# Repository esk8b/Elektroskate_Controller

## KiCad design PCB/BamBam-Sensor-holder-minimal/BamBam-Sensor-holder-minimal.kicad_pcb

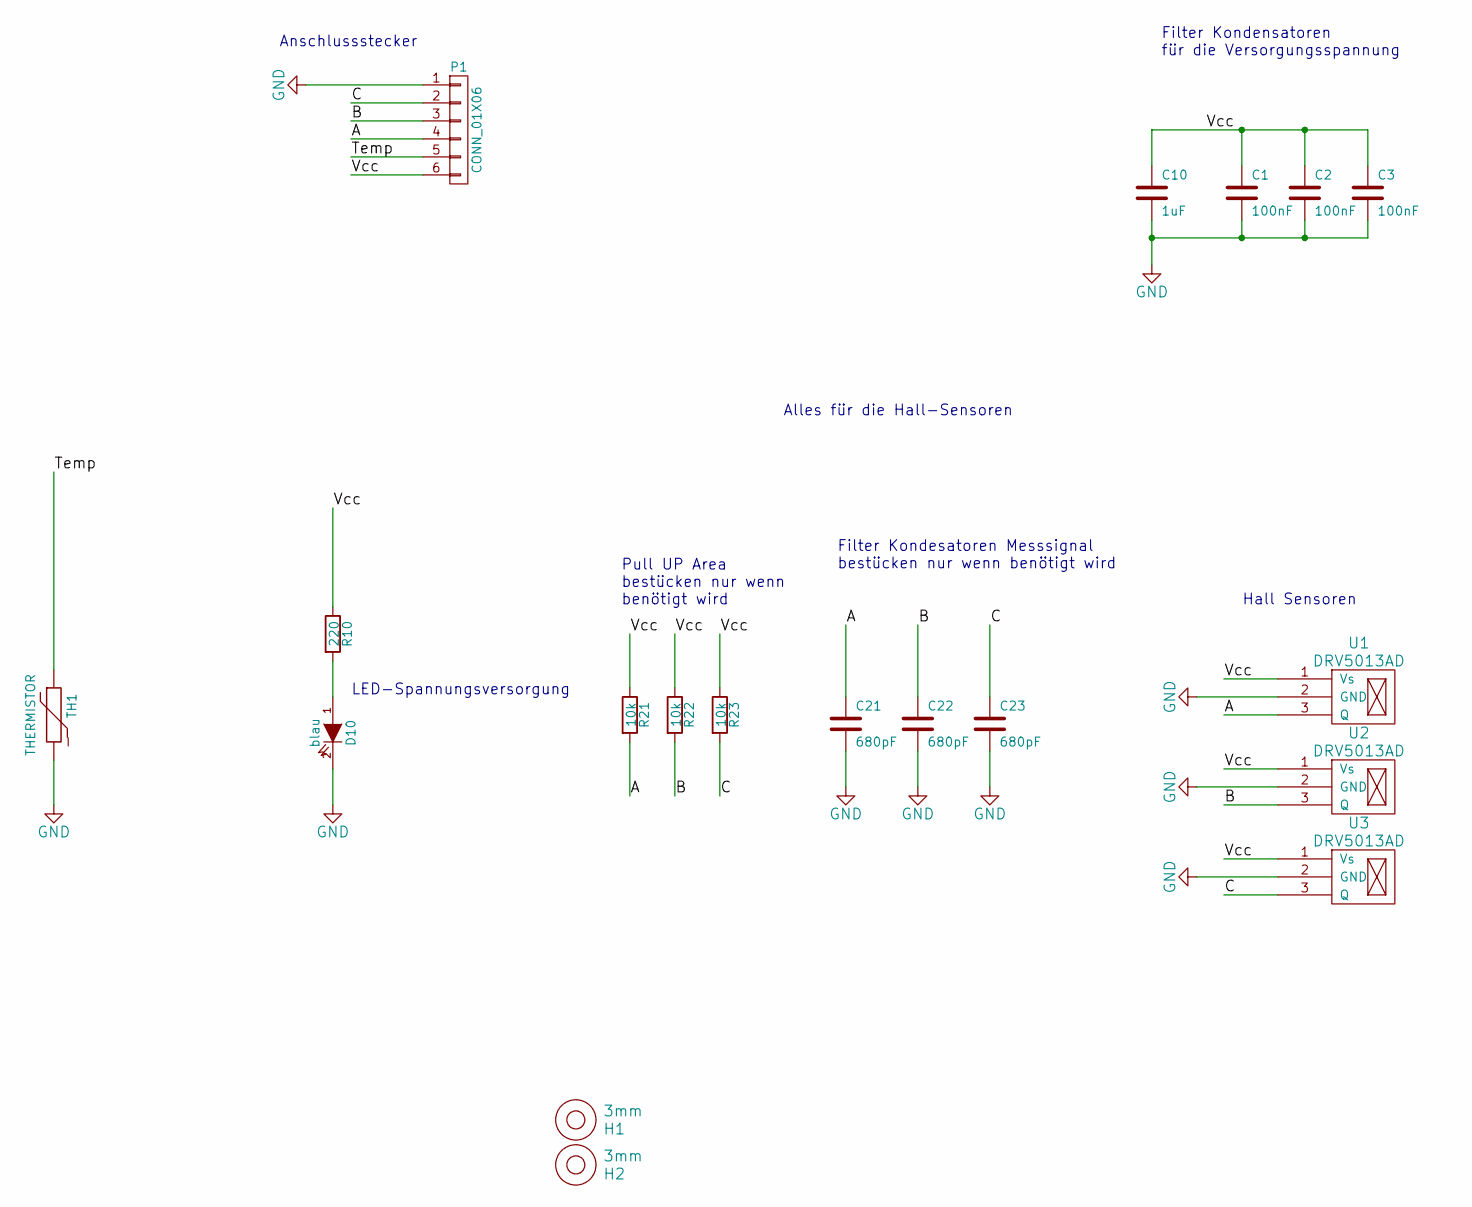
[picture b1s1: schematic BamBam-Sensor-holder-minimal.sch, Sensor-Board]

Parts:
C1, C2, C3: 100nF; R_1206
C10: 1uF; R_1206
C21, C22, C23: 680pF; R_1206
D10: blau; LED-0805
H1, H2: 3mm; MountingHole_3mm
P1: CONN_01X06; B6B-ZR
R10: 220; R_1206
R21, R22, R23: 10k; R_1206
TH1: THERMISTOR; R1
U1, U2, U3: DRV5013AD; P-SSO-3-2

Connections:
/A: C21.1, P1.4, R21.2, U1.3 (Q)
/B: C22.1, P1.3, R22.2, U2.3 (Q)
/C: C23.1, P1.2, R23.2, U3.3 (Q)
/Temp: P1.5, TH1.1
/Vcc: C1.1, C2.1, C3.1, C10.1, P1.6, R10.1, R21.1, R22.1, R23.1, U1.1 (Vs), U2.1 (Vs), U3.1 (Vs)
GND: C1.2, C2.2, C3.2, C10.2, C21.2, C22.2, C23.2, D10.2 (K), P1.1, TH1.2, U1.2 (GND), U2.2 (GND), U3.2 (GND)
unnamed: D10.1 (A), R10.2

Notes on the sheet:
Pull UP Area bestücken nur wenn benötigt wird
LED-Spannungsversorgung
Anschlussstecker
Filter Kondensatoren für die Versorgungsspannung
Hall Sensoren
Filter Kondesatoren Messsignal bestücken nur wenn benötigt wird
Alles für die Hall-Sensoren

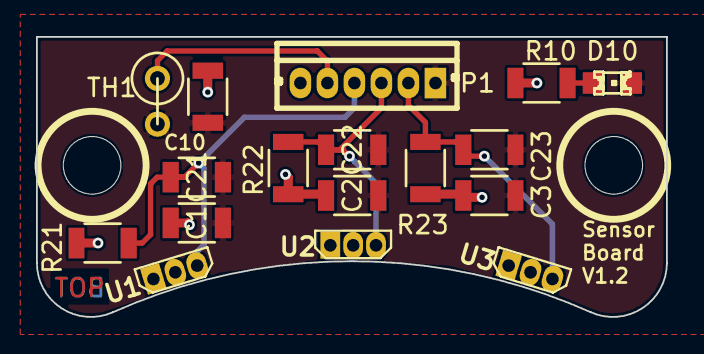
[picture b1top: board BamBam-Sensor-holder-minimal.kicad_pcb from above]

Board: 2 copper layers, 35.0 x 15.6 mm, 19 parts (0 on the bottom side), 7 nets.

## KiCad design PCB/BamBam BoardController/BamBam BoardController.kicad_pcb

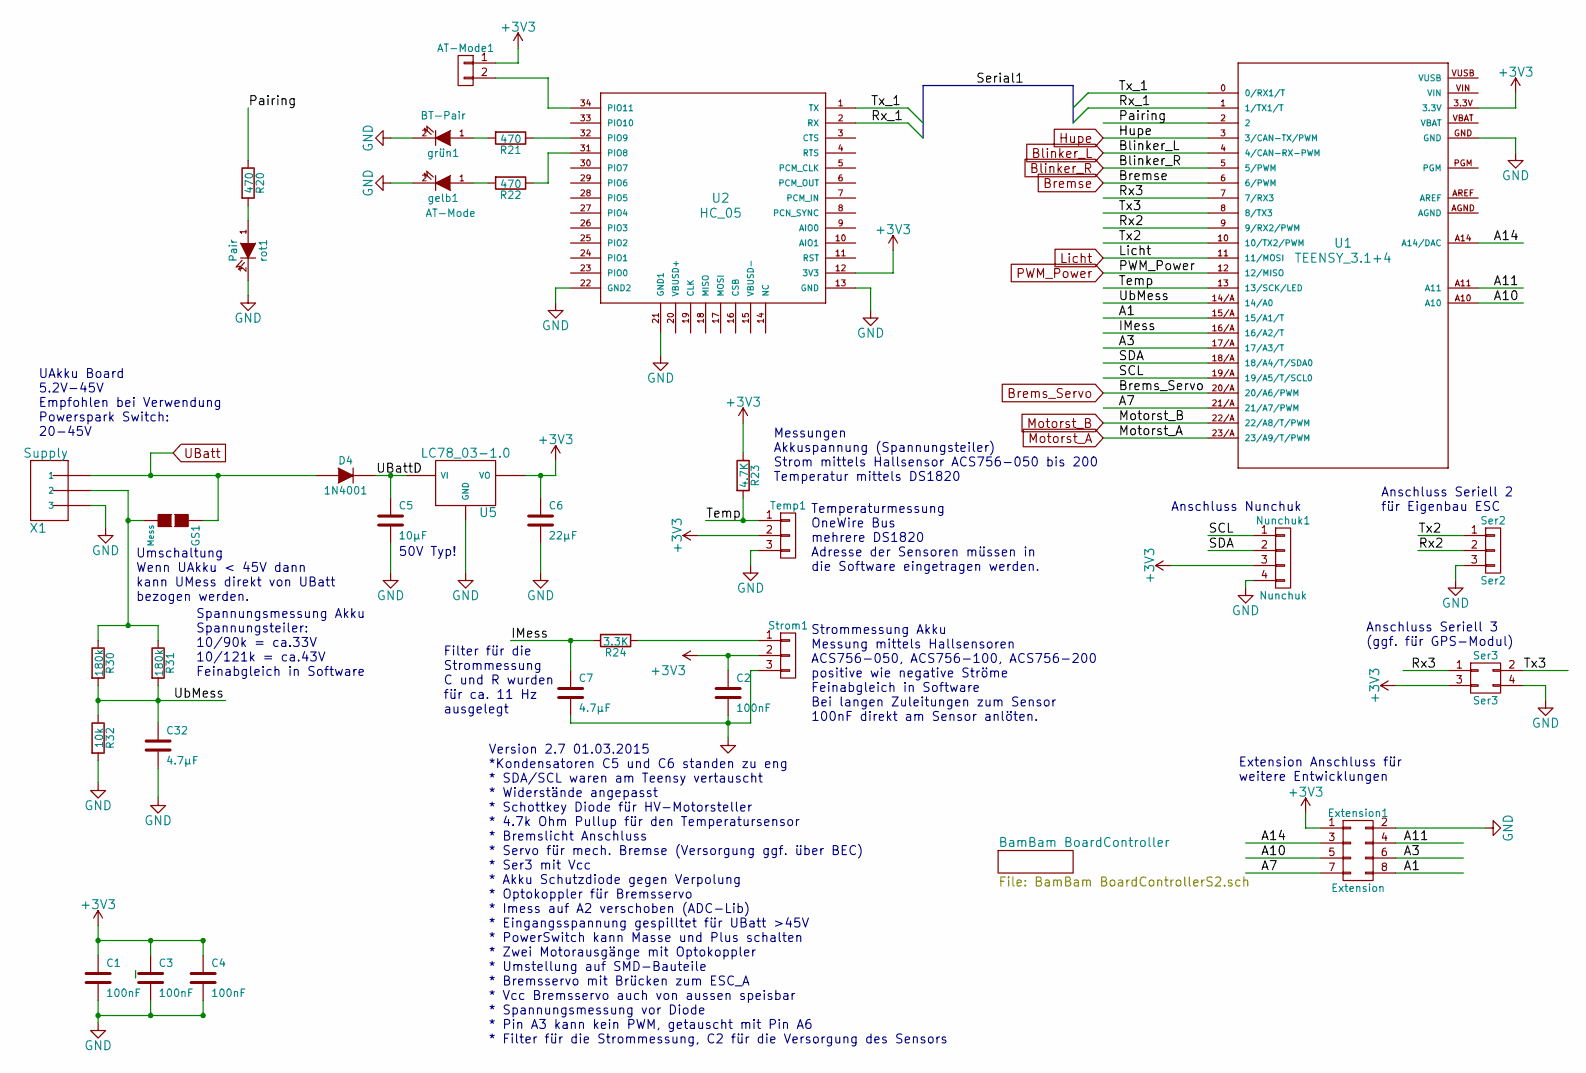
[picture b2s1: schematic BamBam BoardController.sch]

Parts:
AT-Mode1: AT-Mode; Pin_Header_Straight_1x02
C1, C2, C3, C4: 100nF; C_1206
C5: 10µF; C_1206
C6: 22µF; C_1206
C7, C32: 4.7µF; C_1206
D4: 1N4001; SOD123F-REFLOW
Extension1: Extension; Pin_Header_Straight_2x04
GS1: Mess; GS2
Nunchuk1: Nunchuk; Pin_Header_Straight_1x04
R20, R21, R22: 470; R_1206
R23: 4.7K; R_1206
R24: 3.3K; R_1206
R30, R31: 180k; R_1206
R32: 10k; R_1206
Ser2: Ser2; Pin_Header_Angled_1x03
Ser3: Ser3; Pin_Header_Straight_2x02
Strom1: Strom; Pin_Header_Angled_1x03
Temp1: Temp; Pin_Header_Angled_1x03
U1: TEENSY_3.1+4; Teensy_3_Series_Board_v1.0-TEENSY_3.1+4
U2: HC_05; ITEAD_HC-05
U5: LC78_03-1.0; Gaptec-LC78_03
X1: Supply; con-pss254_reichelt-03W
gelb1: AT-Mode; LED-0805
grün1: BT-Pair; LED-0805
rot1: Pair; LED-0805

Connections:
+3V3: AT-Mode1.1, C1.1, C2.1, C3.1, C4.1, C6.1, Extension1.1, Nunchuk1.3, R23.1, Ser3.3, Strom1.2, Temp1.2, U1.3.3V, U2.12 (3V3), U5.3 (VO); also elsewhere on the board
/A1: Extension1.8, U1.15/A (15/A1/T)
/A3: Extension1.6, U1.17/A (17/A3/T)
/A7: Extension1.7, U1.21/A (21/A7/PWM)
/A10: Extension1.5, U1.A10
/A11: Extension1.4, U1.A11
/A14: Extension1.3, U1.A14 (A14/DAC)
/IMess: C7.1, R24.2, U1.16/A (16/A2/T)
/Pairing: R20.1, U1.2
/Rx2: Ser2.2, U1.9 (9/RX2/PWM)
/Rx3: Ser3.1, U1.7 (7/RX3)
/Rx_1: U1.1 (1/TX1/T), U2.2 (RX)
/SCL: Nunchuk1.1, U1.19/A (19/A5/T/SCL0)
/SDA: Nunchuk1.2, U1.18/A (18/A4/T/SDA0)
/Temp: R23.2, Temp1.1, U1.13 (13/SCK/LED)
/Tx2: Ser2.1, U1.10 (10/TX2/PWM)
/Tx3: Ser3.2, U1.8 (8/TX3)
/Tx_1: U1.0 (0/RX1/T), U2.1 (TX)
/UBattD: C5.1, D4.2 (K), U5.1 (VI)
/UbMess: C32.1, R30.2, R31.2, R32.1, U1.14/A (14/A0)
Blinker_L: U1.4 (4/CAN-RX-PWM); also elsewhere on the board
Blinker_R: U1.5 (5/PWM); also elsewhere on the board
Brems_Servo: U1.20/A (20/A6/PWM); also elsewhere on the board
Bremse: U1.6 (6/PWM); also elsewhere on the board
GND: C1.2, C2.2, C3.2, C4.2, C5.2, C6.2, C7.2, C32.2, Extension1.2, Nunchuk1.4, R32.2, Ser2.3, Ser3.4, Strom1.3, Temp1.3, U1.GND, U1.GND1 (GND), U2.13 (GND), U2.21 (GND1), U2.22 (GND2), U5.2 (GND), X1.P$3 (3), gelb1.2 (K), grün1.2 (K), rot1.2 (K); also elsewhere on the board
Hupe: U1.3 (3/CAN-TX/PWM); also elsewhere on the board
Licht: U1.11 (11/MOSI); also elsewhere on the board
Motorst_A: U1.23/A (23/A9/T/PWM); also elsewhere on the board
Motorst_B: U1.22/A (22/A8/T/PWM); also elsewhere on the board
unnamed: AT-Mode1.2, U2.34 (PIO11)
unnamed: GS1.2 (G2), R30.1, R31.1, X1.P$2 (2)
unnamed: R20.2, rot1.1 (A)
unnamed: R21.1, U2.32 (PIO9)
unnamed: R21.2, grün1.1 (A)
unnamed: R22.1, U2.31 (PIO8)
unnamed: R22.2, gelb1.1 (A)
unnamed: R24.1, Strom1.1
PWM_Power: U1.12 (12/MISO); also elsewhere on the board
UBatt: D4.1 (A), GS1.1 (G1), X1.P$1 (1); also elsewhere on the board

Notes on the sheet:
Extension Anschluss für weitere Entwicklungen
Version 2.7 01.03.2015 *Kondensatoren C5 und C6 standen zu eng * SDA/SCL waren am Teensy vertauscht * Widerstände angepasst * Schottkey Diode für HV-Motorsteller * 4.7k Ohm Pullup für den Temperatursensor * Bremslicht Anschluss * Servo für mech. Bremse (Versorgung ggf. über BEC) * Ser3 mit Vcc * Ak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
Anschluss Nunchuk
Anschluss Seriell 2 für Eigenbau ESC
Anschluss Seriell 3 (ggf. für GPS-Modul)
Strommessung Akku Messung mittels Hallsensoren ACS756-050, ACS756-100, ACS756-200 positive wie negative Ströme Feinabgleich in Software Bei langen Zuleitungen zum Sensor 100nF direkt am Sensor anlöten.
Temperaturmessung OneWire Bus mehrere DS1820 Adresse der Sensoren müssen in die Software eingetragen werden.
UAkku Board 5.2V-45V Empfohlen bei Verwendung Powerspark Switch: 20-45V
Umschaltung Wenn UAkku < 45V dann kann UMess direkt von UBatt bezogen werden.
Spannungsmessung Akku Spannungsteiler: 10/90k = ca.33V 10/121k = ca.43V Feinabgleich in Software
Messungen Akkuspannung (Spannungsteiler) Strom mittels Hallsensor ACS756-050 bis 200 Temperatur mittels DS1820
Filter für die Strommessung C und R wurden für ca. 11 Hz ausgelegt
50V Typ!

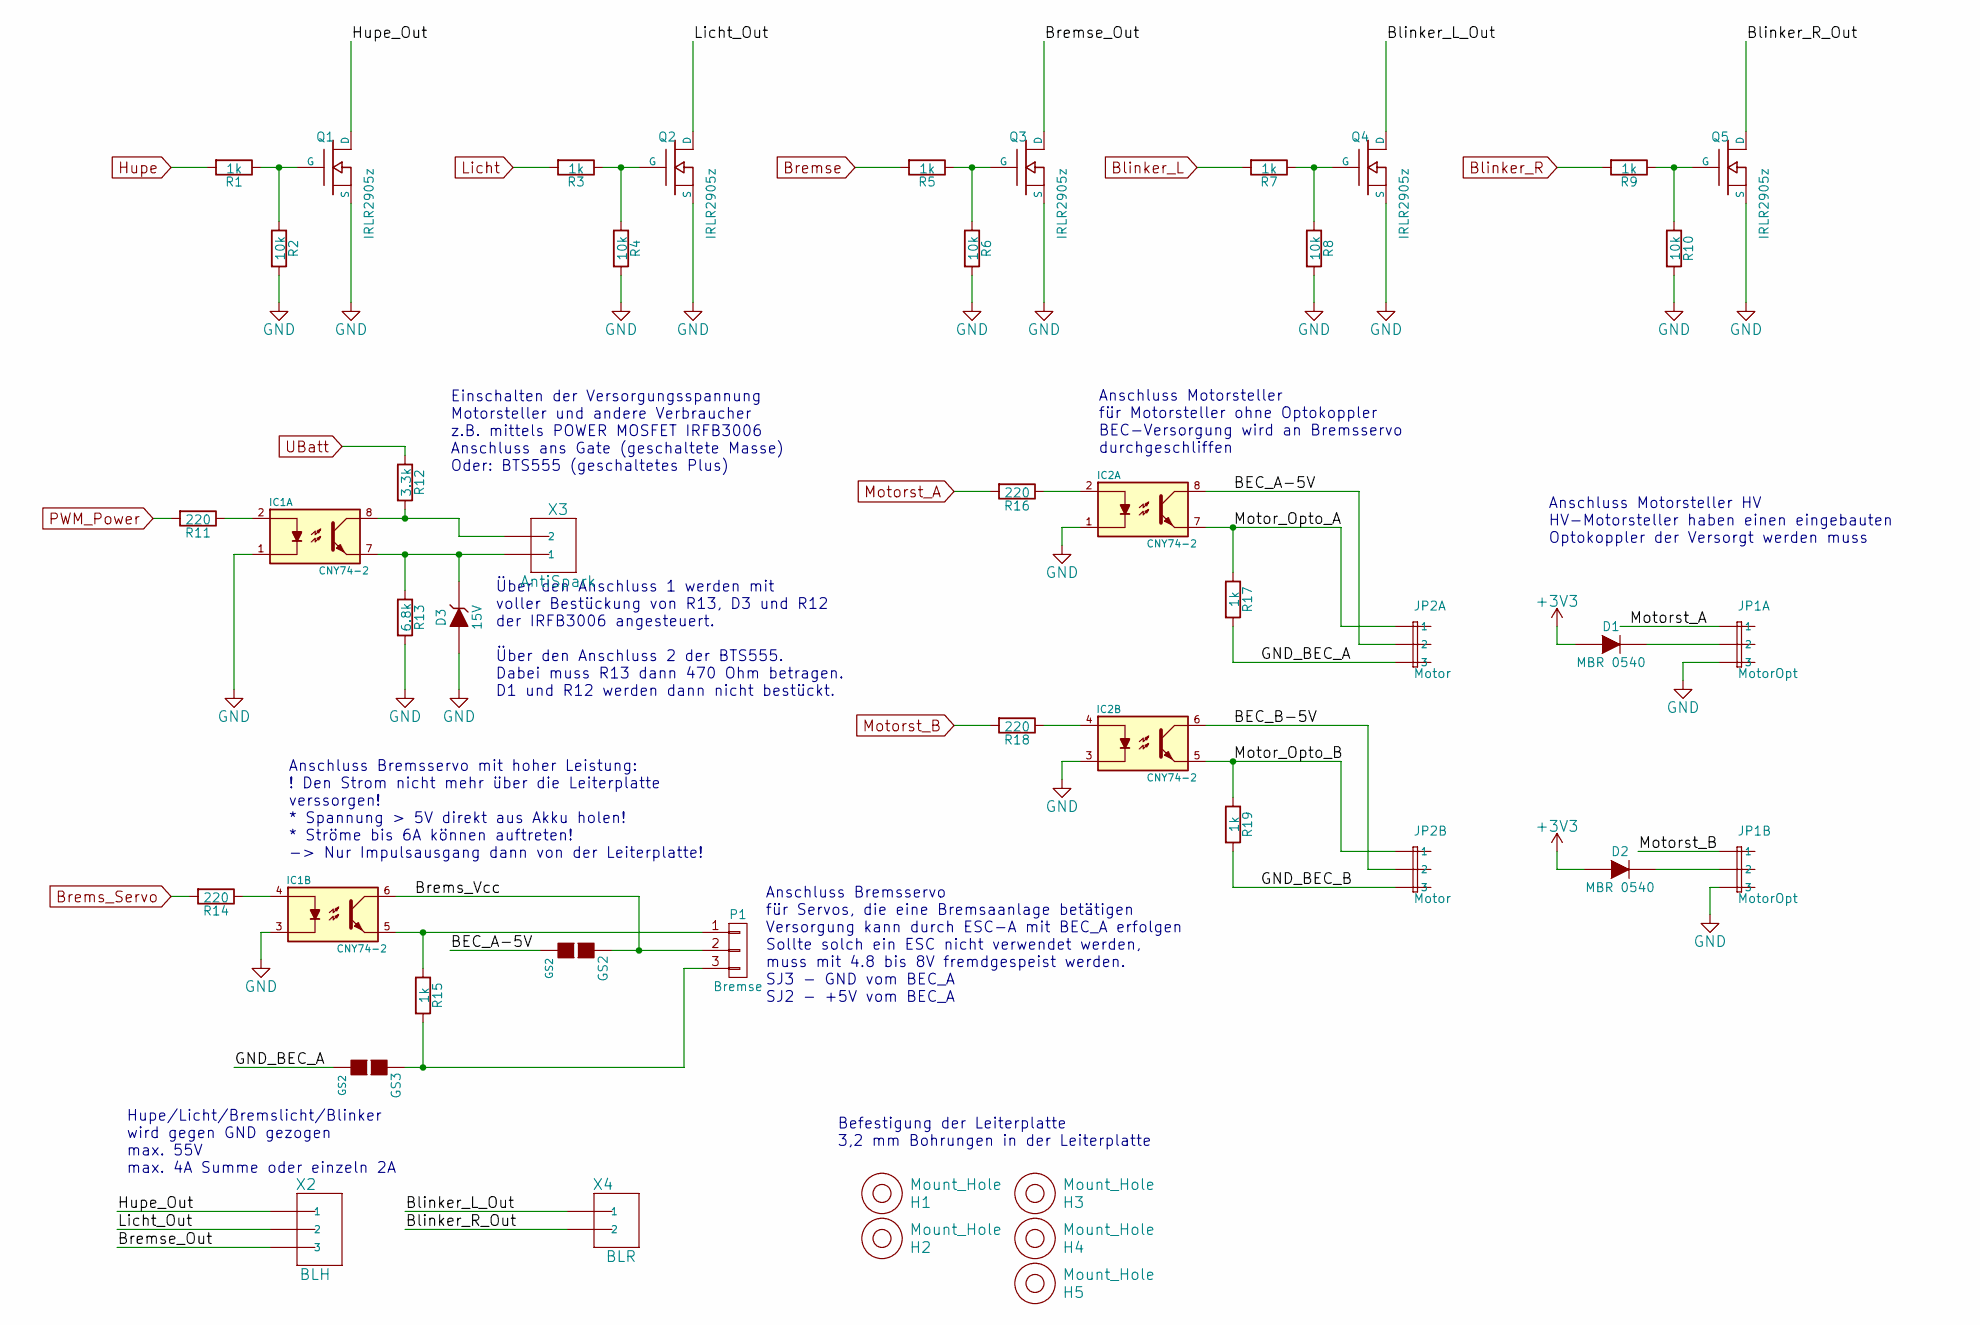
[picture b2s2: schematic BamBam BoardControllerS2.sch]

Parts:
D1, D2: MBR 0540; SOD-123
D3: 15V; DO-35
GS2, GS3: GS2
H1, H2, H3, H4, H5: Mount_Hole; MountingHole_3mm_new
IC1, IC2: CNY74-2; DIP-8__300
JP1: MotorOpt; connector-JP3Q
JP2: Motor; connector-JP3Q
P1: Bremse; Pin_Header_Angled_1x03
Q1, Q2, Q3, Q4, Q5: IRLR2905z; DPAK-3_GDS
R1, R3, R5, R7, R9, R15, R17, R19: 1k; R_1206
R2, R4, R6, R8, R10: 10k; R_1206
R11, R14, R16, R18: 220; R_1206
R12: 3.3k; R_1206
R13: 6.8k; R_1206
X2: BLH; con-pss254_reichelt-03W
X3: AntiSpark; con-pss254_reichelt-02W
X4: BLR; con-pss254_reichelt-02W

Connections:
+3V3: D1.1 (A), D2.1 (A); also elsewhere on the board
/BamBam BoardController/BEC_A-5V: GS2.2 (G2), IC2.8, JP2.2A (2)
/BamBam BoardController/BEC_B-5V: IC2.6, JP2.2B (2)
/BamBam BoardController/Blinker_L_Out: Q4.D, X4.P$1 (1)
/BamBam BoardController/Blinker_R_Out: Q5.D, X4.P$2 (2)
/BamBam BoardController/Brems_Vcc: GS2.1 (G1), IC1.6, P1.2
/BamBam BoardController/Bremse_Out: Q3.D, X2.P$3 (3)
/BamBam BoardController/GND_BEC_A: GS3.2 (G2), JP2.3A (3), R17.2
/BamBam BoardController/GND_BEC_B: JP2.3B (3), R19.2
/BamBam BoardController/Hupe_Out: Q1.D, X2.P$1 (1)
/BamBam BoardController/Licht_Out: Q2.D, X2.P$2 (2)
/BamBam BoardController/Motor_Opto_A: IC2.7, JP2.1A (1), R17.1
/BamBam BoardController/Motor_Opto_B: IC2.5, JP2.1B (1), R19.1
Blinker_L: R7.2; also elsewhere on the board
Blinker_R: R9.2; also elsewhere on the board
Brems_Servo: R14.2; also elsewhere on the board
Bremse: R5.2; also elsewhere on the board
GND: D3.1 (A), IC1.1, IC1.3, IC2.1, IC2.3, JP1.3A (3), JP1.3B (3), Q1.S, Q2.S, Q3.S, Q4.S, Q5.S, R2.2, R4.2, R6.2, R8.2, R10.2, R13.2; also elsewhere on the board
Hupe: R1.2; also elsewhere on the board
Licht: R3.2; also elsewhere on the board
Motorst_A: JP1.1A (1), R16.2; also elsewhere on the board
Motorst_B: JP1.1B (1), R18.2; also elsewhere on the board
unnamed: D1.2 (K), JP1.2A (2)
unnamed: D2.2 (K), JP1.2B (2)
unnamed: D3.2 (K), IC1.7, R13.1, X3.P$1 (1)
unnamed: GS3.1 (G1), P1.3, R15.2
unnamed: IC1.2, R11.1
unnamed: IC1.4, R14.1
unnamed: IC1.5, P1.1, R15.1
unnamed: IC1.8, R12.2, X3.P$2 (2)
unnamed: IC2.2, R16.1
unnamed: IC2.4, R18.1
unnamed: Q1.G, R1.1, R2.1
unnamed: Q2.G, R3.1, R4.1
unnamed: Q3.G, R5.1, R6.1
unnamed: Q4.G, R7.1, R8.1
unnamed: Q5.G, R9.1, R10.1
PWM_Power: R11.2; also elsewhere on the board
UBatt: R12.1; also elsewhere on the board

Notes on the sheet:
Hupe/Licht/Bremslicht/Blinker wird gegen GND gezogen max. 55V max. 4A Summe oder einzeln 2A
Einschalten der Versorgungsspannung Motorsteller und andere Verbraucher z.B. mittels POWER MOSFET IRFB3006 Anschluss ans Gate (geschaltete Masse) Oder: BTS555 (geschaltetes Plus)
Über den Anschluss 1 werden mit voller Bestückung von R13, D3 und R12 der IRFB3006 angesteuert. Über den Anschluss 2 der BTS555. Dabei muss R13 dann 470 Ohm betragen. D1 und R12 werden dann nicht bestückt.
Anschluss Motorsteller für Motorsteller ohne Optokoppler BEC-Versorgung wird an Bremsservo durchgeschliffen
Anschluss Bremsservo mit hoher Leistung: ! Den Strom nicht mehr über die Leiterplatte verssorgen! * Spannung > 5V direkt aus Akku holen! * Ströme bis 6A können auftreten! -> Nur Impulsausgang dann von der Leiterplatte!
Anschluss Bremsservo für Servos, die eine Bremsaanlage betätigen Versorgung kann durch ESC-A mit BEC_A erfolgen Sollte solch ein ESC nicht verwendet werden, muss mit 4.8 bis 8V fremdgespeist werden. SJ3 - GND vom BEC_A SJ2 - +5V vom BEC_A
Anschluss Motorsteller HV HV-Motorsteller haben einen eingebauten Optokoppler der Versorgt werden muss
Befestigung der Leiterplatte 3,2 mm Bohrungen in der Leiterplatte

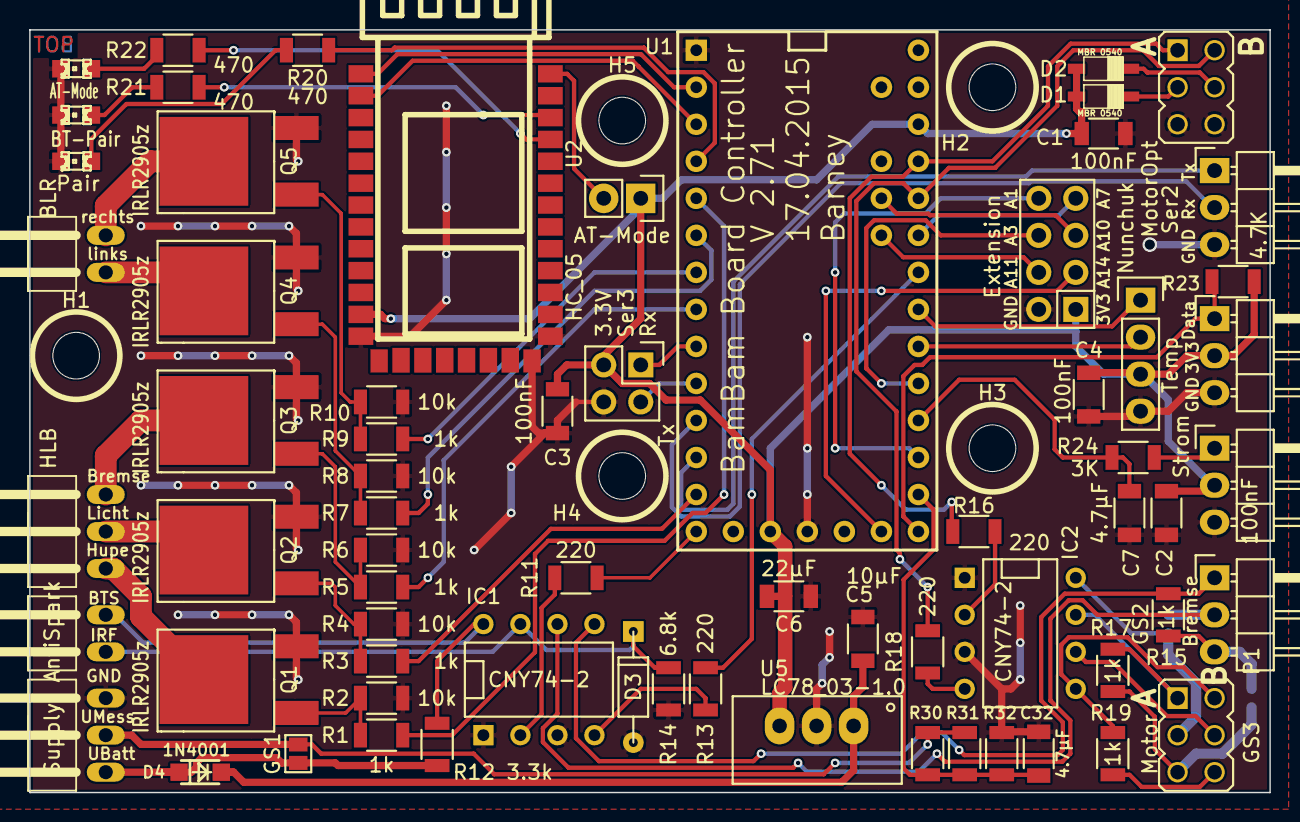
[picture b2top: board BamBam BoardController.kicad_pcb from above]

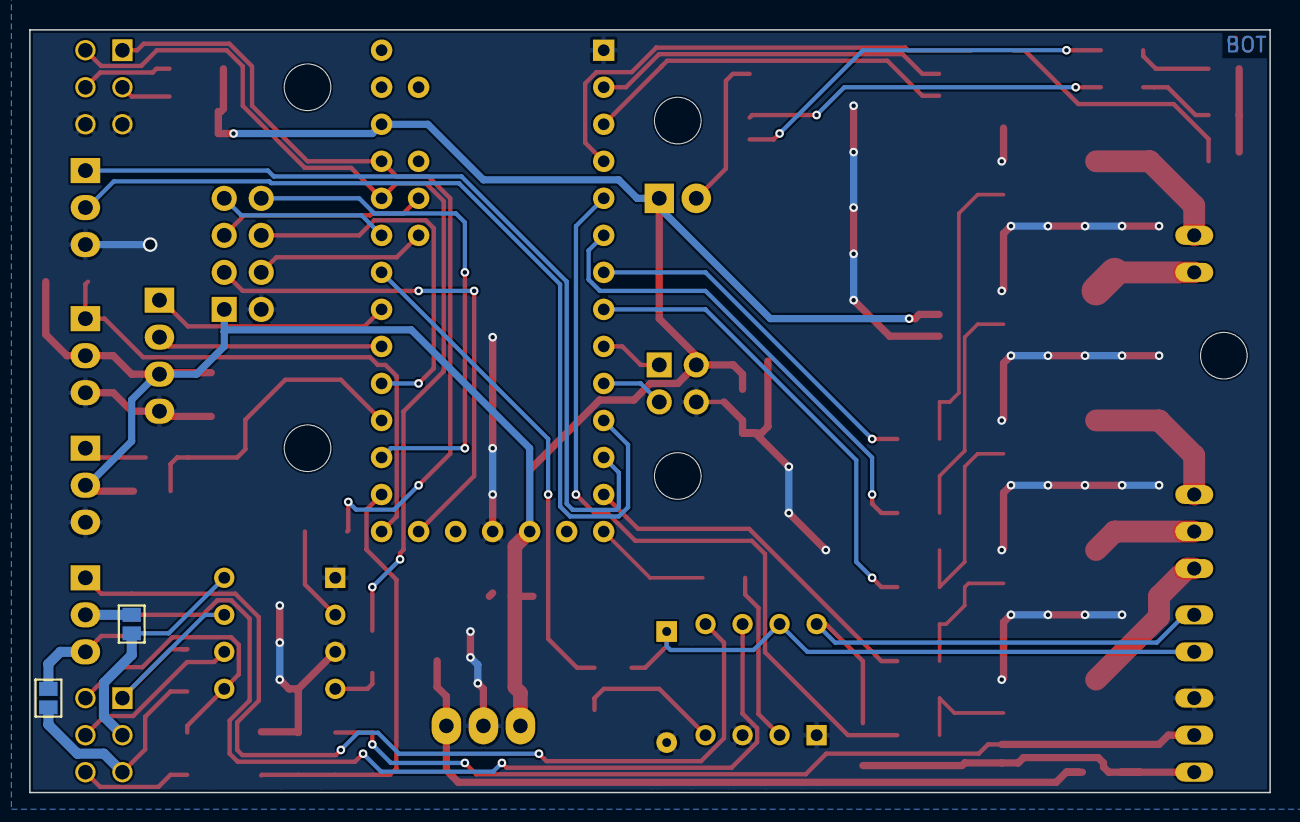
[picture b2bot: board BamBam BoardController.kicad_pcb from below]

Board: 2 copper layers, 85.1 x 52.3 mm, 74 parts (2 on the bottom side), 66 nets.

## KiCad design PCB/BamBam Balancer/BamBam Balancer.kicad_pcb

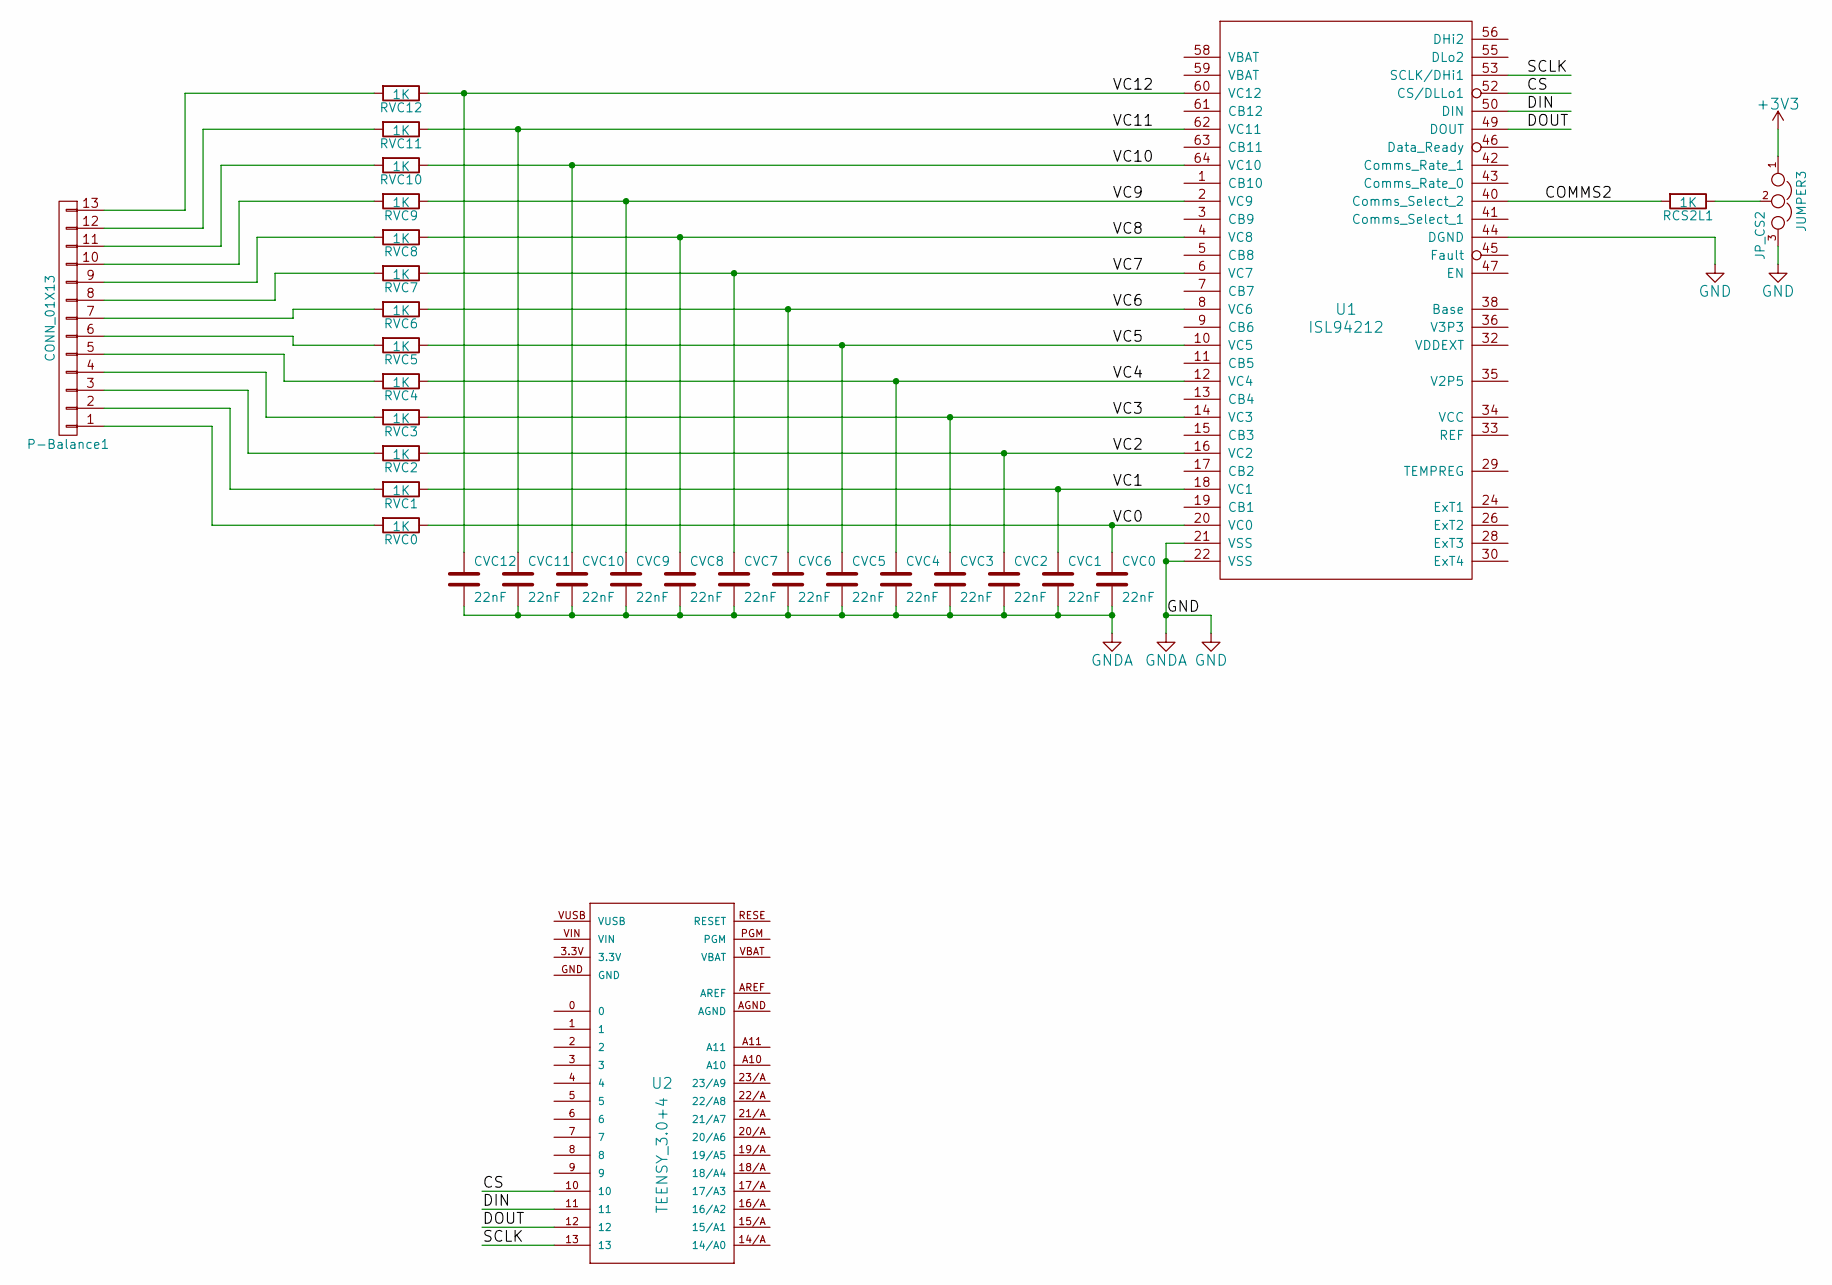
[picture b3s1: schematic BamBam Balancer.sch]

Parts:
CVC0, CVC1, CVC2, CVC3, CVC4, CVC5, CVC6, CVC7, CVC8, CVC9, CVC10, CVC11, CVC12: 22nF; C_1206
JP_CS2: JUMPER3; GS3
P-Balance1: CONN_01X13; Pin_Header_Angled_1x13
RCS2L1: 1K; R_1206
RVC0, RVC1, RVC2, RVC3, RVC4, RVC5, RVC6, RVC7, RVC8, RVC9, RVC10, RVC11, RVC12: 1K; R_1206
U1: ISL94212; TQFP-64_10x10mm_Pitch0.5mm
U2: TEENSY_3.0+4; Teensy_3_Series_Board_v1.0-TEENSY_3.1+4

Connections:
3.3V: U2.3.3V
+3V3: JP_CS2.1; also elsewhere on the board
/COMMS2: RCS2L1.2, U1.40 (Comms_Select_2)
/CS: U1.52 (CS/DLLo1), U2.10
/DIN: U1.50 (DIN), U2.11
/DOUT: U1.49 (DOUT), U2.12
/SCLK: U1.53 (SCLK/DHi1), U2.13
/VC0: CVC0.1, RVC0.1, U1.20 (VC0)
/VC1: CVC1.1, RVC1.1, U1.18 (VC1)
/VC2: CVC2.1, RVC2.1, U1.16 (VC2)
/VC3: CVC3.1, RVC3.1, U1.14 (VC3)
/VC4: CVC4.1, RVC4.1, U1.12 (VC4)
/VC5: CVC5.1, RVC5.1, U1.10 (VC5)
/VC6: CVC6.1, RVC6.1, U1.8 (VC6)
/VC7: CVC7.1, RVC7.1, U1.6 (VC7)
/VC8: CVC8.1, RVC8.1, U1.4 (VC8)
/VC9: CVC9.1, RVC9.1, U1.2 (VC9)
/VC10: CVC10.1, RVC10.1, U1.64 (VC10)
/VC11: CVC11.1, RVC11.1, U1.62 (VC11)
/VC12: CVC12.1, RVC12.1, U1.60 (VC12)
unnamed: JP_CS2.2, RCS2L1.1
unnamed: P-Balance1.1, RVC0.2
unnamed: P-Balance1.2, RVC1.2
unnamed: P-Balance1.3, RVC2.2
unnamed: P-Balance1.4, RVC3.2
unnamed: P-Balance1.5, RVC4.2
unnamed: P-Balance1.6, RVC5.2
unnamed: P-Balance1.7, RVC6.2
unnamed: P-Balance1.8, RVC7.2
unnamed: P-Balance1.9, RVC8.2
unnamed: P-Balance1.10, RVC9.2
unnamed: P-Balance1.11, RVC10.2
unnamed: P-Balance1.12, RVC11.2
unnamed: P-Balance1.13, RVC12.2

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
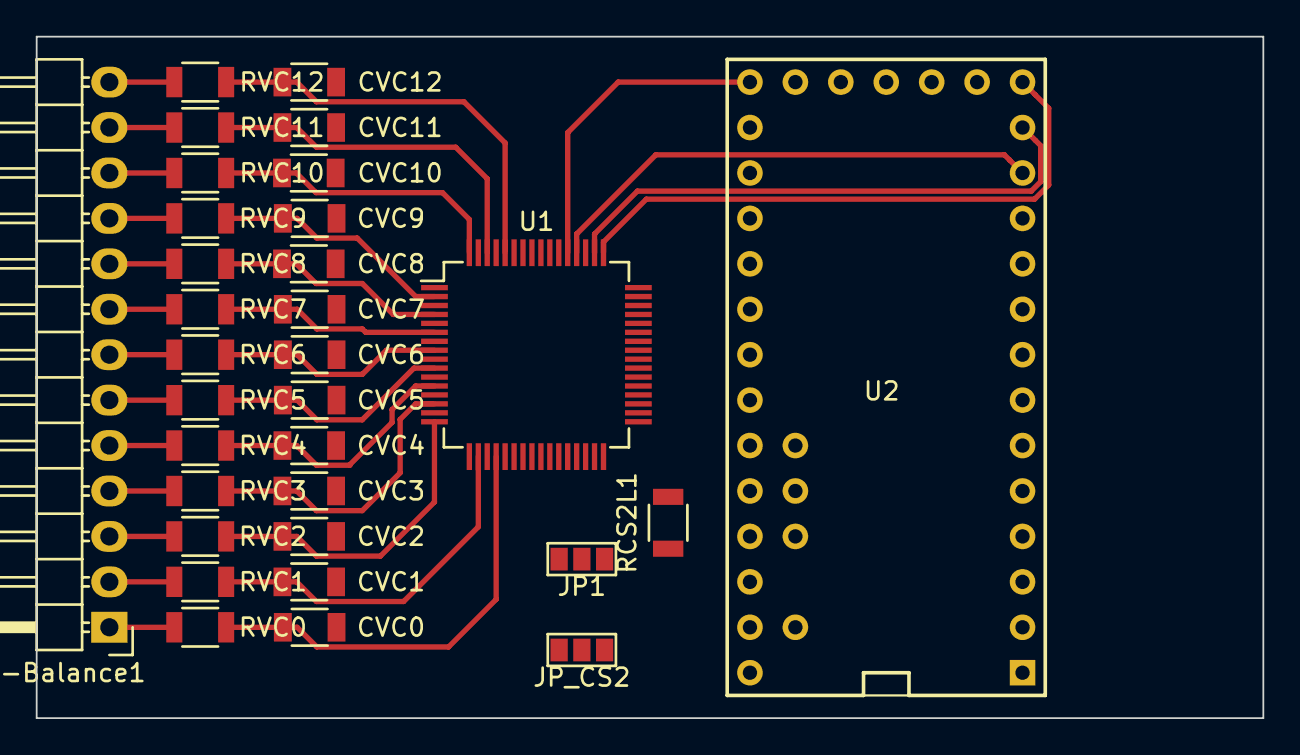
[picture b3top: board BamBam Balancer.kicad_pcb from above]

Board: 2 copper layers, 68.6 x 38.1 mm, 32 parts (0 on the bottom side), 34 nets.

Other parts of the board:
JP1: JUMPER3; GS3

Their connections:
+3V3: JP1.1; also elsewhere on the board

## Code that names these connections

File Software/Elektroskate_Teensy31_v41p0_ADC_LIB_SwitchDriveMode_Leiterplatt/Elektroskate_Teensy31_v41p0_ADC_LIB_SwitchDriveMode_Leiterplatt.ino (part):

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uint8_t  PairingStatus = LOW;          // Beim Einschalten besteht kein Pairing
uint16_t PairingLostCounter = 0;       // wird hoch gezaehlt, wenn accelX hintereinander gleiche Werte liefert
uint16_t PairingSuccessCounter = 0;    // wird hoch gezaehlt, wenn accelX hintereinander ungleiche Werte liefert
uint16_t accelXAlt = 0;                // Alter Beschleunigungswert X fuers Pairing und Funkabrisserkennung

// PWM Motorsteuerung
#define PWMFrequenz 50                 // PWM Frequenz fuer die Ansteuerung des Motorstellers: alle 20ms einen Impuls in der Laenge von 1.0 bis 2.0ms
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uint16_t TempSensor;

// Ubatt, Strom und Leistungsmessung
float Ubatt = 0;                      // Spannung Batterie in V gemessen
float Strom[10] = {0};                // Strommessung Array, der Strom kann auch negativ werden, es wird ein Array zum Mitteln verwendet
uint16_t StromIndex = 0;              // Zeiger fuer den Strom
float Momentanleistung = 0;           // Aktuelle Leistung, die gerade aufgenommen wird
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#define StromFaktor (float) 2*StromMMax/AnalogReadResolutionValue  // Umrechnungsfaktor Strom

// Strombegrenzung und Kurzschlusserkennung
#define Reduktionsgewichtung (float) (100/(Ishort-Imax)) // Der Reduktionsfaktor Bf = 100-((Imess-Imax)*Reduktionsgewichtung) in %
float Reduktionsfaktor = 0;           // Reduktionsfaktor(%): Stellwert = (Stellwertmomentan-Motorneutralstellung)*Reduktionsfaktor + Motorneutralstellung
float Imomentan = 0;                  // Momentanstrom, wird abgeleitet von Strom[0] oder Ishort
uint8_t F_Ueberstrom = LOW;           // Sollte ein Uebserstrom erkannt werden, wird eine Reduzierung des Motorstellwertes durchgefuehrt
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void setup()
{
  // ADC Einstellungen
  pinMode(Pin_Ubatt, INPUT);                            // Spannungsmesspin aktivieren
  pinMode(Pin_Strom, INPUT);                            // Strommesspin aktivieren
  // ADC_0
  adc->setReference(ADC_REF_EXT, ADC_0);           // Bei Extern wird die ca. 3.3V Versorgungsspannung des Teensys benutzt
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  adc->setSamplingSpeed(ADC_VERY_LOW_SPEED, ADC_1);     // change the sampling speed
  // Continuous Abfragemodus kann erst ab Platine v2.5 verwendet werden (Verwendung der Pins A0, A2 statt A0, A1)
  // Abfragezeit der ADC sinkt unter 4us.
  adc->startContinuous(Pin_Ubatt, ADC_0);               // Starte die Dauermessung der beiden ADC im Hintergrund
  adc->startContinuous(Pin_Strom, ADC_1);               // Dies beschleunigt die Messwerterfassung um das 150-fache
                                                        // (damit wird auch die Verwendung einer hohen Meßwertanzahl zum Averaging möglich)
  adc->analogReadContinuous(ADC_0);                     // Messwertabfrage des ADC_0 ab (Achtung asynchron)
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  // DAC Einstellungen
  analogWriteFrequency(Pin_Motorstelleranschluss_A, PWMFrequenz); // Einstellen der PWM Parameter fuer den Motorsteller
  analogWriteFrequency(Pin_Motorstelleranschluss_B, PWMFrequenz); // Einstellen der PWM Parameter fuer den Motorsteller
  analogWriteFrequency(Pin_Brems_Servo, PWMFrequenz);             // Einstellen der PWM Parameter fuer den Motorsteller
  analogWriteResolution(AnalogWriteResolutionBits);               // Analog Aufloesung auf 16 Bit einstellen

  // Zyklischer IRQ-Timer die einen Software Interrupt ausloest
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  Serial1.begin(BT_BAUDRATE);    // Werteausgabe ueber Serieller mittels Bluetooth definieren

  // Alle Ausgangspins definieren
  pinMode(Pin_Hupe, OUTPUT);          // Hupe ist ein Ausgang
  pinMode(Pin_Licht, OUTPUT);         // Licht ist ein Ausgang
  pinMode(Pin_Bremse, OUTPUT);        // Bremslicht ist ein Ausgang
  pinMode(Pin_Blinker_L, OUTPUT);     // Blinker Links ist ein Ausgang
  pinMode(Pin_Blinker_R, OUTPUT);     // Blinker Rechts ist ein Ausgang
  pinMode(Pin_ReceiverLED, OUTPUT);   // ReceiverLED ist ein Ausgang
  pinMode(Pin_PowerSwitch, OUTPUT);   // Power MOSFET ist ein Ausgang

  // Startwert der Ausgaenge definieren
  digitalWrite(Pin_Hupe, LOW);        // Hupe aus
  digitalWrite(Pin_Licht, LOW);       // Licht aus
  digitalWrite(Pin_Bremse, LOW);      // Bremslicht aus
  digitalWrite(Pin_Blinker_L, LOW);   // Blinker Links aus
  digitalWrite(Pin_Blinker_R, LOW);   // Blinker Rechts aus
  digitalWrite(Pin_ReceiverLED, LOW); // Empfangsstatus LED aus

  // Leistungselektronik ueber PWM soft hochfahren
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    StellWertMotor = LeerlaufStellWertMotor;                            // StellWertMotor auf Leerlauf setzen
    analogWrite(Pin_Motorstelleranschluss_A, LeerlaufStellWertMotor);   // PWM Register Motorstellwert-A auf Leerlauf
    analogWrite(Pin_Motorstelleranschluss_B, LeerlaufStellWertMotor);   // PWM Register Motorstellwert-B auf Leerlauf
    analogWrite(Pin_Brems_Servo, PWM_Bremse_Ungebremst * AnalogWriteResolutionValue * PWMFrequenz / 1000); // PWM Register Bremsservo auf Bremse loesen
    PairingSuccessCounter = 0;                                          // ParingSuccessCounter zuruecksetzen
    while (PairingStatus == LOW) {                                      // Solange pruefen, bis die Verbindung steht
      accelXAlt = accelX;                                               // Alten Wert des Beschleunigungssensors ablegen
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void Funkabriss() {
  // Totmannschalter und Funkabriss pruefen
  if (DEBUG_Funktion) Serial_B.println("Funktion: Funkabriss");
  digitalWrite(Pin_ReceiverLED, HIGH);              // Pairing steht, Status ReceiverLED an
  accelXAlt = accelX;
  Nunchuk_auslesen();
  if (accelX == accelXAlt || accelXAlt > 1024) {    // Wahrscheinlichkeitspruefung Funkabriss
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  // Bremsservostellwert und Bremslicht setzen

  if (StellWertMotor <  LeerlaufStellWertMotor) {
    digitalWrite(Pin_Bremse, HIGH);                    // Bremslicht an
    analogWrite(Pin_Brems_Servo, StellWertBremse_max); // PWM Register Bremsservo auf Vollbremse
    if (DEBUG_Bremse) {
      Serial_B.print("PWM_Bremse_Vollbremse: ");
      Serial_B.println(StellWertBremse_max);
    }
  }
  else {
    digitalWrite(Pin_Bremse, LOW);                     // Bremslicht aus
    analogWrite(Pin_Brems_Servo, StellWertBremse_off); // PWM Register Bremsservo auf Bremse loesen
    if (DEBUG_Bremse) {
      Serial_B.print("PWM_Bremse_Ungebremst: ");
      Serial_B.println(StellWertBremse_off);
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  if (DEBUG_Funktion) Serial_B.println("Funktion: Licht_Hupe");
  if (cButton == LOW) cButtonZero = LOW;                           // Trigger auf ansteigende Flanke, damit Licht nicht blinkt
  if (cButton == HIGH && cButtonZero == LOW && analogX_12bit < XAchseLinks_12bit) {  // Toggle Licht Nunchuck X < 30
    digitalWrite(Pin_Licht, !digitalRead(Pin_Licht));
    cButtonZero = HIGH;                                            // Licht gegen Blinken sperren
  }
  if (cButton == HIGH && analogX_12bit > XAchseLinks_12bit) {      // Hupe an solange C-Taste gedrueckt und X > 30
    digitalWrite(Pin_Hupe, HIGH);
  }
  else {
    digitalWrite(Pin_Hupe, LOW);
  }
}

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  // Licht und Hupe benutzen den selben Taster sind aber durch die Nunchuk X-Achse getrennt
  if (DEBUG_Funktion) Serial_B.println("Funktion: BlinkerRL");
  if (analogX_12bit < XAchseLinks_12bit) {  // Blinker Links wenn Nunchuck X < XAchseLinks
    digitalWrite(Pin_Blinker_L, HIGH);      // Blinker Links an
  }
  if (analogX_12bit > XAchseRechts_12bit) { // Blinker Rechts wenn Nunchuck X > XAchseRechts
    digitalWrite(Pin_Blinker_R, HIGH);      // Blinker Rechts an
  }
  else {
    digitalWrite(Pin_Blinker_L, LOW);       // Blinker Links aus
    digitalWrite(Pin_Blinker_R, LOW);       // Blinker Rechts aus
  }
}

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    }

    if (LICHTHUPE) {
      digitalWrite(Pin_Hupe, HIGH);                  // Zur Bestaetigung 200ms hupen
      delay (200);
      digitalWrite(Pin_Hupe, LOW);
    }
    zButtonZero = HIGH;                              // Routine gegen Festhalten des Z-Tasters sperren
    if (ObererStellWertMotorUmschaltCounter == 3) {  // Es muss dreimal die Z-Taste und der X-Joystick ausgeloest werden
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      }   
      ObererStellWertMotorUmschaltCounter = 0;       // Counter zuruecksetzen
      if (LICHTHUPE) {
        digitalWrite(Pin_Hupe, HIGH);                // Zur Bestaetigung der Umschaltung 500ms hupen
        delay (500);
        digitalWrite(Pin_Hupe, LOW);
      } 
    }
  }
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    }

    if (LICHTHUPE) {
      digitalWrite(Pin_Hupe, HIGH);      // Zur Bestaetigung 200ms hupen
      delay (200);
      digitalWrite(Pin_Hupe, LOW);
    }
    zButtonZero = HIGH;                  // Routine gegen Festhalten des Z-Tasters sperren
    if (DriveModeUmschaltCounter == 3) { // Es muss dreimal die Z-Taste und der X-Joystick ausgeloest werden
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      DriveModeUmschaltCounter = 0;       // Counter zuruecksetzen
      LeerlaufStellWertMotor = float(PWM_LeerlaufStellWertMotor*AnalogWriteResolutionValue*PWMFrequenz/1000) + (LeerlaufOffset * !DirectDrive); // Update Leerlaufstellwert
      if (LICHTHUPE) {
        digitalWrite(Pin_Hupe, HIGH);     // Zur Bestaetigung der Umschaltung 500ms hupen
        delay (500);
        digitalWrite(Pin_Hupe, LOW);
      }
    }
  }
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
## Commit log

2015-01-11 4.1p0-28.12.2014 Barney: Die Leiterplattenversion v2.5 hat jetzt den Stromsensor an A2. Dadurch kann die ADC-Lib die beiden ADCs getrennt im Teensy parametrieren. Durch die neue Leiterplatte wird der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
2015-01-11 Neue Ordnerstruktur
2015-01-14 Die Strom und Spannungsmessung erfolgt jetzt über die zwei eingebauten ADC-Kanäle ADC_0 und ADC_1. Die Mittelwertbildung wurde von 8 auf 32 angehoben. Eine Messung würde 433µs dauern, es wurde aber d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
2015-01-31 Umstellung auf die Nunchuk Teensy Lib
2015-03-03 Anpassung der Software auf Teensyduino 1.22 und Arduino 1.6.x
2015-03-03 KiCad Projektdateien
2015-03-03 Aktuelle KiCad Datei
2015-03-05 Aktuelle KiCad Daten
2015-03-09 Anpassungen in KiCad PCB Mount Hole hat jetzt die Bohrung 3.2mm Werte der Bauteile nicht mit "," sondern ".". Wichtig für den Export der BOM Bessere Verlegung der Spannungsmessleitung, geschützt in G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
2015-03-21 Anpassung an Arduino IDE 1.61 und Teensyduino 1.21
2015-03-28 Auf BamBam angepasst. HC-05 Rahmen lag auf Pads BrmesOpto Text durch Bremse erstezt Gerber und Drill-Dateien generiert und gesichtet
2015-03-31 Bohrungen für die PC352 und PC353, sowie für die Motorstiftleisten auf 0.965 bzw. 1.0mm vergrößert. Zwei Leiterbahnen wegen Kollisionsmöglichkeit verschoben. Text auf Leiterplatte auf BamBam und Datu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
2015-04-16 Anpassung an die KiCAD Libs >02/2015 Einige kleine Korrekturen am Layout Anpassung der Mounting Holes mit NTPH (nicht durch kontaktieren) Zwei Texte im PCB zugefügt (Tx und Rx Ser2)
2015-04-19 Ab Teensyduino 1.22 wird die Lib ADC und i2c_t3 mitgeliefert und wurde daher aus der library gelöscht. Die Umschaltung DirectDrive und Integraldrive wurde deaktiviert. Die Umschaltung muss gegen vers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
2015-05-01 Files komplett mit aktuellen Dateien aus Barneys zip-Archiv überschrieben.
2015-05-11 Die Version 2.71 hat einige Veränderungen in den Bestückungstext bekommen, Verdeckte Texte wurden Verlagert und noch weitere Informationen an den Anschlüssen ergänzt. Eine Leiterbahn wurde im Quersch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
2015-05-18 Software: Polynom für die Spannungsmessung
2015-05-18 Software: Polynom Spannungsmessung
2015-06-10 4.1p4-28.05.2015 Dude - DEBUG-Flag aus Settings.h entfernt, da ohne Verwendung. Verallgemeinerung der Ausgabe auf 2 generelle Ausgabekanle (USBSerial und BT) - Update Kommentare - Motorsteller-Offset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
2015-06-17 xls mit Augleichspolynom
2015-06-29 Anpassung fuer Arduino 1.6.5.r2 und Teensyduino 1.24 adc.h adc->setReference(ADC_REF_EXT, ADC_0); siehe Dokumentation adc Lib
2015-07-14 Die Libs für den Teensy sind jetzt wieder bei.
2016-12-30 Add files via upload
    Notaus-Anschluss, hält den Motor an, wenn Reißleinenanschluss unterbrochen wird.
2017-09-09 Anpassung Entwicklungsumgebung
    An die aktuelle Arduino 1.8.4 und Teensyduino 1.32 Version
    ADC.h wurde verändert

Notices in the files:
Software/Elektroskate_Teensy31_v41p0_ADC_LIB_SwitchDriveMode_Leiterplatt/Elektroskate_Teensy31_v41p0_ADC_LIB_SwitchDriveMode_Leiterplatt.ino:
Copyright (C) [2012]  [Barney]
This program is free software; you can redistribute it and/or modify it under the terms of
the GNU General Public License as published by the Free Software Foundation; either
Dieses Programm ist freie Software. Sie koennen es unter den Bedingungen der GNU General Public License,
wie von der Free Software Foundation veroeffentlicht, weitergeben und/oder modifizieren,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
